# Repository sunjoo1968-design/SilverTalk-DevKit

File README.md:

# SilverTalk DevKit

제작자 SunjooAn · 갤럭시 앱 1.10 · ESP32 DevKit 펌웨어 1.8

SilverTalk는 ESP32-WROOM-32 박스의 물리 버튼으로 갤럭시에서 AI 음성 대화를 시작하고 마이크를 제어합니다. USB 또는 Wi-Fi로 박스를 연결하고, 보호자가 A·B 위치에 ChatGPT, Gemini Live, Sesame, Pi를 배정할 수 있습니다. 음성 입출력은 갤럭시의 마이크와 스피커를 사용합니다.

## 설치와 사용

[GitHub 배포 ZIP](https://github.com/sunjoo1968-design/SilverTalk-DevKit/releases/latest)에는 갤럭시 APK, 기존 박스 업데이트용 펌웨어, 새 박스 설치용 통합 펌웨어, 설치 안내와 배선도가 들어 있습니다.

- [설치와 보호자 설정](devkit-controller/docs/설치안내.md)
- [ESP32 펌웨어 플래싱 상세 안내](devkit-controller/docs/펌웨어-플래싱.md)
- [GPIO 배선도](devkit-controller/docs/배선도.svg)와 [부품표](devkit-controller/docs/부품표.md)

통화 중 대기 버튼을 3초 눌러 연속 대화를 켜고, 짧게 눌러 음소거 대기로 돌아옵니다. 선택 사양인 연속 대화 전용 버튼은 GPIO33, 전용 LED는 GPIO13에 연결합니다.

앱 1.10은 서비스 전환 중 선택이 다시 바뀌면 마지막 스위치 위치를 기준으로 통화를 유지합니다. 앱 1.9에서 수정한 짧은 Wi-Fi 지연 대응도 포함합니다. 다른 기종에서는 PD 충전과 USB 호스트 동시 동작 및 사용할 AI 앱의 마이크 제어를 설치할 때 확인하세요.

## 프로토타입 PCB

PCB r1.0은 30핀 ESP32-WROOM-32 DevKit을 두 줄의 암헤더에 끼우고, 스위치·LED·OLED를 JST XH로 연결하는 84 × 74 mm 캐리어입니다.

- [PCB 제작·조립 안내와 국내 부품 구매 링크](devkit-controller/hardware/carrier-r1.0/README.md)
- [PCB 주문용 거버 ZIP](https://github.com/sunjoo1968-design/SilverTalk-DevKit/releases/download/pcb-r1.0/SilverTalk-DevKit-Carrier-r1.0-JLCPCB-Gerber.zip)
- [KiCad 설계 전체 ZIP](https://github.com/sunjoo1968-design/SilverTalk-DevKit/releases/download/pcb-r1.0/SilverTalk-DevKit-Carrier-r1.0.zip)

## 프로토타입 케이스 r1.0

84 × 74 mm 캐리어용 본체, 교체형 전면판, 분리형 상판과 갤럭시 가로·세로 거치대를 포함합니다.

- [JLC3DP용 STL ZIP](https://github.com/sunjoo1968-design/SilverTalk-DevKit/releases/download/case-r1.0/SilverTalk-DevKit-Case-r1.0-JLC3DP.zip)
- [주문·조립 안내와 1:1 전면 도면](devkit-controller/hardware/enclosure-r1.0/README.md)

## 소스 빌드

### 갤럭시 앱

Windows PowerShell, JDK 17 이상, Android SDK Platform 36과 Build Tools 35.0.0을 사용합니다.

```powershell
.\devkit-controller\android\Build-Android.ps1 -AndroidSdk 'C:\Android\Sdk'
```

결과는 `devkit-controller/android/build/SilverTalk-DevKit-unsigned.apk`입니다. 새로 빌드한 APK는 본인 keystore로 서명할 수 있습니다. 배포 APK 위에 덮어 설치하려면 같은 서명이 필요하므로 일반 설치에는 GitHub Release의 서명된 APK를 사용하세요.

### ESP32 펌웨어

ESP-IDF 5.5.6 환경에서 실행합니다.

```powershell
Set-Location .\devkit-controller\firmware
idf.py set-target esp32
idf.py build
```

앱 영역 업데이트 파일은 `build/silvertalk_controller.bin`입니다. 초기 설치에는 `idf.py -p COM20 flash` 또는 배포 ZIP의 통합 파일을 사용합니다. COM 번호는 PC에서 확인한 값으로 바꿉니다.

## 제작 정보

음성 제어 흐름은 Sesami · ChatGPT Pro Micro V1 샘플을 참고했습니다. Android USB 시리얼 코드의 저작자와 라이선스는 [USB-SERIAL-LICENSE.txt](devkit-controller/android/USB-SERIAL-LICENSE.txt)에 있습니다.

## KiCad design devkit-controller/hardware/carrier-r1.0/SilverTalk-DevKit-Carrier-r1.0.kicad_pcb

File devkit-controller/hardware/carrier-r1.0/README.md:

# SilverTalk DevKit 캐리어 PCB r1.0

제작자 SunjooAn · 갤럭시 앱 1.10 · ESP32 DevKit 펌웨어 1.8

SilverTalk의 패널 부품을 배선 하네스로 꽂고, ESP32 DevKit을 교체할 수 있는 2층 캐리어입니다. 대상은 ESP32-WROOM-32 USB-C DevKit 중 **양쪽 15핀, 한 줄 피치 2.54 mm, 두 줄 중심 간격 25.00 mm**인 보드입니다.

## 주문 전 맞춤 확인

- 부품면에서 안테나를 위로 두었을 때 왼쪽 줄 맨 위는 `EN`, 오른쪽 줄 맨 위는 `23`입니다. USB-C 쪽 왼쪽 끝은 `VIN`, 오른쪽 끝은 `3V3`입니다. 보드의 인쇄 표기와 키캐드 회로도에서 이 방향과 실제 GPIO 순서를 확인하세요.
- [소켓 맞춤 1:1 도면](소켓맞춤-1대1.svg)을 100%로 인쇄하고, 도면의 25 mm 선을 자로 확인한 뒤 DevKit을 얹어 보세요. 두 줄 중심은 25.00 mm이며, 각 줄의 첫 핀부터 끝 핀까지는 35.56 mm입니다.
- 두 개의 독립 암헤더를 DevKit에 먼저 끼우고 캐리어의 홈에 넣어 위치를 맞춥니다. 가로 2.00 × 세로 1.00 mm 도금 슬롯 안에서 암헤더를 맞춘 다음 두 줄의 끝 핀을 먼저 납땜하세요. DevKit을 뺐다가 다시 끼워 맞춤을 확인한 뒤 나머지 핀을 납땜합니다.

## PCB 주문

JLC3DP에서 **PCB/PCBA** 메뉴를 선택하면 JLCPCB의 PCB 주문 화면으로 이동합니다. 그 화면에 `SilverTalk-DevKit-Carrier-r1.0-JLCPCB-Gerber.zip`을 올리세요. [JLC3DP 공식 주문 안내](https://jlc3dp.com/help/article/how-to-combine-orders-for-jlc3dp-and-jlcpcb-products)

| 항목 | 주문 설정 |
| --- | --- |
| 소재·층수 | FR-4, 2층 |
| 외곽 크기 | 84 × 74 mm. 위쪽 안테나 홈 36 × 12 mm, 아래쪽 USB-C 케이블 홈 14 × 12 mm |
| 형태·수량 | Standard PCB/PCBA · Single PCB · Different Design 1 · 프로토타입 5장 |
| 두께·동박 | 1.6 mm, 외층 1 oz |
| 색상·표면처리 | Green · White 실크 · LeadFree HASL |
| 조립 | PCB Assembly 끔 · Stencil 끔. 스루홀 부품은 직접 납땜 |
| 드릴 | PTH 62개 중 가로 도금 슬롯 30개, NPTH Ø3.2 mm 고정 홀 4개 |
| 슬롯 옵션 | Blind Slots No. 소켓 슬롯은 기판을 관통하는 2.00 × 1.00 mm 도금 슬롯 |
| 제조 파일 확인 | Confirm Production File Yes · Do not confirm automatically 체크 |

JLCPCB 견적 화면에서 2층과 84 × 74 mm 인식을 확인했고, 뷰어의 드릴 레이어에서 소켓 슬롯 30개와 고정 홀 4개를 확인했습니다. 주문 전 미리보기에서 같은 외곽과 홀을 대조하세요. ZIP에는 거버 7개, Excellon 드릴 2개, 거버 작업 정보가 들어 있습니다. [JLCPCB 거버·드릴 안내](https://jlcpcb.com/help/article/how-to-generate-gerber-and-drill-files-in-kicad-8) · [제조 파일 확인 안내](https://jlcpcb.com/kr/help/article/how-to-confirm-the-production-file)

## 커넥터 핀

모든 2핀 커넥터에서 **1번은 신호 또는 LED 양극, 2번은 GND**입니다. PCB의 사각 패드와 짧은 실크 표식이 1번입니다. 스위치는 닫을 때 GPIO를 GND에 연결합니다. 아래 번호는 부품면 기준입니다.

| 커넥터 | 연결 부품 | 1번 | 2번 |
| --- | --- | --- | --- |
| J3 | 서비스 B LED | GPIO32 → R1 → LED 양극 | LED 음극 |
| J4 | 연속 대화 버튼 | GPIO33 | GND |
| J5 | 말하기 PTT 버튼 | GPIO25 | GND |
| J6 | 대기 버튼 LED | GPIO26 → R2 → LED 양극 | LED 음극 |
| J7 | 대기·깨우기 버튼 | GPIO23 | GND |
| J9 | 마이크 LED | GPIO19 → R3 → LED 양극 | LED 음극 |
| J10 | 서비스 A/B 전환 스위치 | GPIO18 | GND |
| J11 | 서비스 A LED | GPIO27 → R4 → LED 양극 | LED 음극 |
| J12 | 연속 대화 LED | GPIO13 → R5 → LED 양극 | LED 음극 |

**J8 OLED**는 1번 GND, 2번 3V3, 3번 SCL(GPIO22), 4번 SDA(GPIO21)입니다. OLED 모듈에 인쇄된 이름끼리 연결하세요. 3.3 V SSD1306 I²C 128×64, 주소 0x3C를 사용합니다.

J10을 개방하면 A, GND에 연결하면 B입니다. J4·J5·J7에는 순간식 NO 버튼을 사용합니다. LED의 저항은 PCB에 장착하므로 각 LED는 해당 커넥터에 양극과 음극을 연결합니다.

## 부품표

| 수량 | 품목과 규격 |
| --- | --- |
| 1 | ESP32-WROOM-32 USB-C DevKit, 30핀, 4MB, 실물 핀 배열 확인 |
| 2 | J1·J2 — 1×15, 2.54 mm, 수직 스루홀 암헤더 |
| 9 | J3–J7, J9–J12 — JST XH 2핀 PCB 헤더 B2B-XH-A 및 짝 하우징 XHP-2 |
| 1 | J8 — JST XH 4핀 PCB 헤더 B4B-XH-A 및 짝 하우징 XHP-4 |
| 22 | JST XH 암 크림프 단자 SXH-001T-P0.6 또는 규격에 맞는 사전 압착 케이블 |
| 5 | R1–R5 — 220 Ω, 1/4 W, 축형, 리드 간격 7.62 mm |
| 5 | 5 mm LED, 낮은 순방향 전압의 고효율형 |
| 3 | 순간식 NO 버튼, 패널 장착형 |
| 1 | 유지형 SPST ON/OFF 스위치, 패널 장착형 |
| 1 | SSD1306 I²C OLED 모듈, 4선 |
| 4 | M3 스페이서와 나사, PCB 홀 Ø3.2 mm |

JST XH 커넥터의 피치는 **2.50 mm**입니다. [JST XH 공식 도면](https://www.jst-mfg.com/product/pdf/eng/eXH.pdf)

## 국내 구매와 직접 압착

다음 수량은 PCB 한 장에 모든 패널 부품을 연결하는 기준입니다.

| 부품 | 필요한 수량 | 국내 구매처 |
| --- | ---: | --- |
| ESP32 소켓. 1×15, 2.54 mm, 수직 스루홀 암헤더 | 2개 | [디바이스마트 1×15 암헤더](https://www.devicemart.co.kr/goods/view?no=12497) |
| PCB용 2핀 수헤더 `B2B-XH-A` | 9개 | [레고전자부품 B2B-XH-A](https://regoelec.co.kr/product/detail.html?product_no=3910) |
| PCB용 4핀 수헤더 `B4B-XH-A` | 1개 | [레고전자부품 B4B-XH-A](https://regoelec.co.kr/product/detail.html?product_no=3912) |
| 배선용 2핀 암 하우징 `XHP-02` | 9개 | [레고전자부품 XHP-02](https://regoelec.co.kr/product/detail.html?product_no=3905) |
| 배선용 4핀 암 하우징 `XHP-04` | 1개 | [레고전자부품 XHP-04](https://regoelec.co.kr/product/detail.html?product_no=3907) |
| 두 하우징에 공통으로 쓰는 암 압착 단자 `SXH-001T-P0.6` | 22개 | [레고전자부품 SXH-001T-P0.6](https://regoelec.co.kr/product/detail.html?product_no=3920) |

암 하우징은 각각 `1EA` 옵션을 선택하고, 압착 단자는 이 판매처의 최소 옵션인 `100EA` 한 팩을 선택합니다. 부품을 확인했을 때 하우징 10개와 단자 한 팩은 합계 2,485원이었으며, 전선과 배송비는 별도입니다.

AWG 26 연선에 암 단자를 압착하고 하우징에 끼웁니다. J8은 **1 GND, 2 3V3, 3 SCL, 4 SDA**를 기준으로 하네스 전선에 표시한 뒤 OLED 모듈의 핀 이름끼리 연결하세요.

완성 하네스를 사용할 경우에는 [로봇사이언스몰 2핀 JST XH 호환 하네스](https://robotscience.kr/goods/view?no=16652) 9세트와 [디바이스마트 4핀 JST XH 호환 하네스](https://www.devicemart.co.kr/goods/view?no=15574781) 1세트를 준비합니다. 각 세트에서 PCB의 수헤더에 꽂히는 전선 쪽 암 커넥터를 사용합니다.

## 조립 후 확인

1. 전원을 분리한 상태에서 암헤더, 저항, JST 헤더를 납땜하고 3V3와 GND 사이 단락 여부를 확인합니다.
2. 안테나가 위쪽 홈을 향하고 USB-C가 아래쪽 홈을 향하도록 DevKit을 끼웁니다. 안테나 위·뒤에 금속 스페이서, 전선 뭉치, 금속 케이스가 가까이 오지 않도록 배치합니다. [Espressif ESP32 안테나 배치 가이드](https://docs.espressif.com/projects/esp-hardware-design-guidelines/en/latest/esp32/pcb-layout-design.html)
3. 각 커넥터에 패널 부품을 꽂고 DevKit 자체 USB-C로 전원을 공급합니다. 유선 제어에는 DevKit USB-C를 기존 갤럭시 PD 허브에 연결합니다.
4. OLED 표시, A/B 전환, 대기 버튼, PTT, 연속 대화 버튼과 해당 LED를 차례로 확인합니다. 펌웨어는 기존 1.8을 그대로 사용합니다. [펌웨어 플래싱 안내](펌웨어-플래싱.md)

## 설계 검증

KiCad 9.0.8에서 전기 규칙 검사(ERC), PCB 설계 규칙 검사(DRC), 회로도와 PCB 대조를 실행했습니다. 각각 0건이며 미연결 패드도 0건입니다. 제조용 거버 외곽은 84 × 74 mm이고, 별도 드릴 파일에 도금 슬롯 30개와 비도금 Ø3.2 mm 홀 4개가 있습니다. 실물 소켓 맞춤과 제작 후 기능 검증은 프로토타입 조립 때 확인합니다.

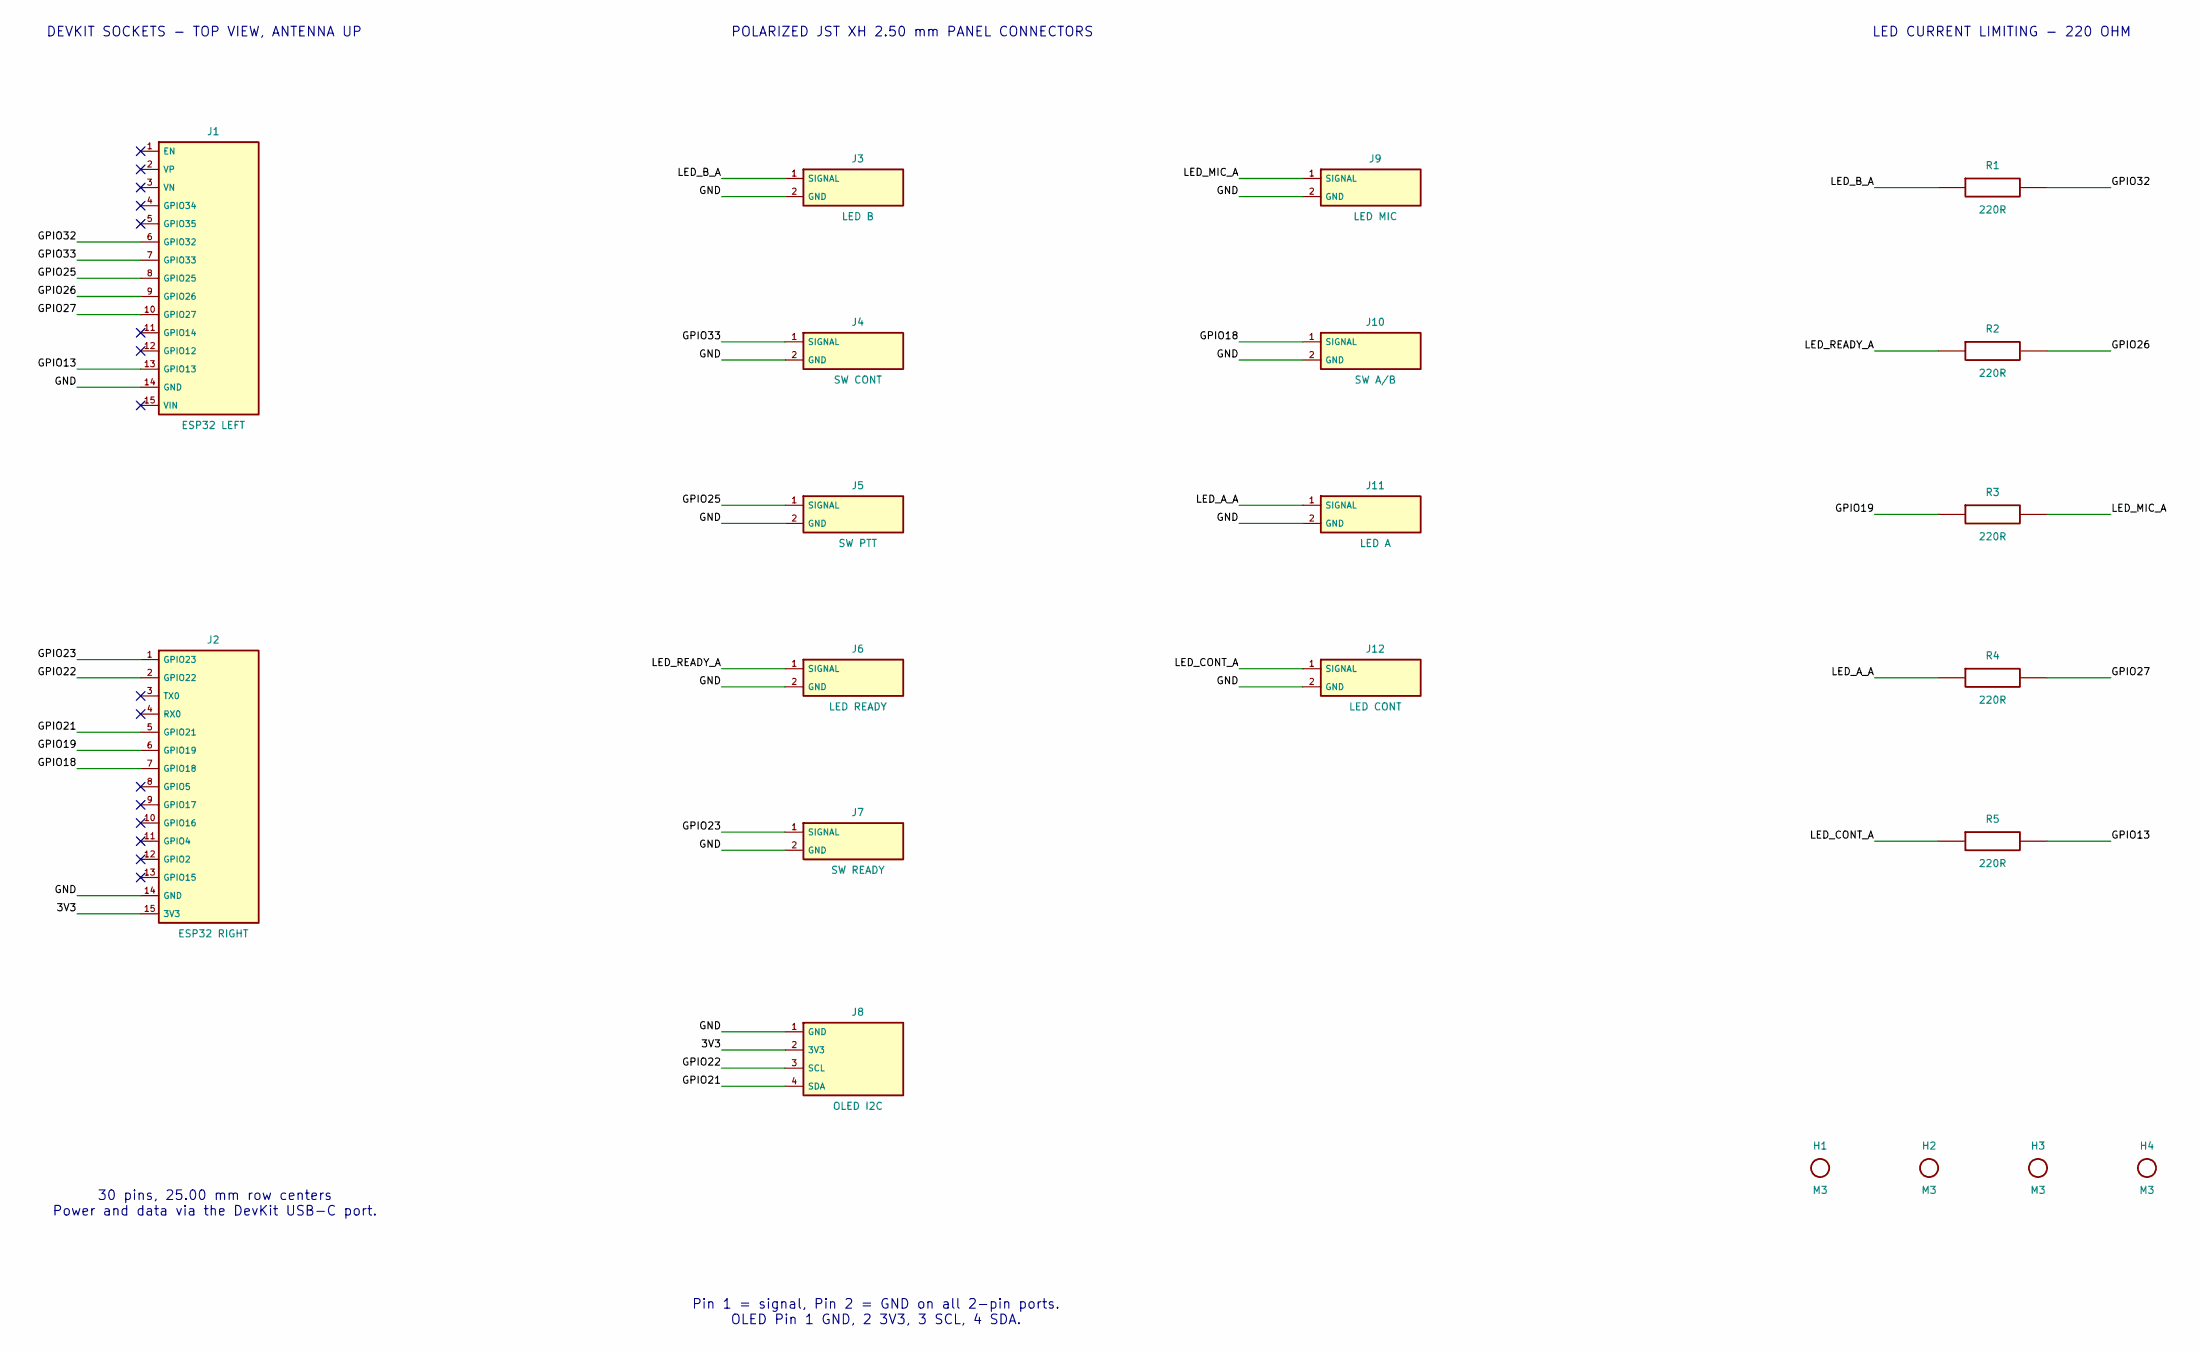
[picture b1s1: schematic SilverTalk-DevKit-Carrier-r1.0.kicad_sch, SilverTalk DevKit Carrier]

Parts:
H1, H2, H3, H4: M3; MountingHole_3.2_M3
J1: ESP32 LEFT; Socket_1x15_P2.54_LateralSlots
J2: ESP32 RIGHT; Socket_1x15_P2.54_LateralSlots
J3: LED B; JST_XH_1x02
J4: SW CONT; JST_XH_1x02
J5: SW PTT; JST_XH_1x02
J6: LED READY; JST_XH_1x02
J7: SW READY; JST_XH_1x02
J8: OLED I2C; JST_XH_1x04
J9: LED MIC; JST_XH_1x02
J10: SW A/B; JST_XH_1x02
J11: LED A; JST_XH_1x02
J12: LED CONT; JST_XH_1x02
R1, R2, R3, R4, R5: 220R; R_Axial_P7.62

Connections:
/3V3: J2.15 (3V3), J8.2 (3V3)
/GND: J1.14 (GND), J2.14 (GND), J3.2 (GND), J4.2 (GND), J5.2 (GND), J6.2 (GND), J7.2 (GND), J8.1 (GND), J9.2 (GND), J10.2 (GND), J11.2 (GND), J12.2 (GND)
/GPIO13: J1.13 (GPIO13), R5.2
/GPIO18: J2.7 (GPIO18), J10.1 (SIGNAL)
/GPIO19: J2.6 (GPIO19), R3.1
/GPIO21: J2.5 (GPIO21), J8.4 (SDA)
/GPIO22: J2.2 (GPIO22), J8.3 (SCL)
/GPIO23: J2.1 (GPIO23), J7.1 (SIGNAL)
/GPIO25: J1.8 (GPIO25), J5.1 (SIGNAL)
/GPIO26: J1.9 (GPIO26), R2.2
/GPIO27: J1.10 (GPIO27), R4.2
/GPIO32: J1.6 (GPIO32), R1.2
/GPIO33: J1.7 (GPIO33), J4.1 (SIGNAL)
/LED_A_A: J11.1 (SIGNAL), R4.1
/LED_B_A: J3.1 (SIGNAL), R1.1
/LED_CONT_A: J12.1 (SIGNAL), R5.1
/LED_MIC_A: J9.1 (SIGNAL), R3.2
/LED_READY_A: J6.1 (SIGNAL), R2.1

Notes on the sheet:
DEVKIT SOCKETS - TOP VIEW, ANTENNA UP
POLARIZED JST XH 2.50 mm PANEL CONNECTORS
LED CURRENT LIMITING - 220 OHM
Pin 1 = signal, Pin 2 = GND on all 2-pin ports. OLED Pin 1 GND, 2 3V3, 3 SCL, 4 SDA.
30 pins, 25.00 mm row centers Power and data via the DevKit USB-C port.

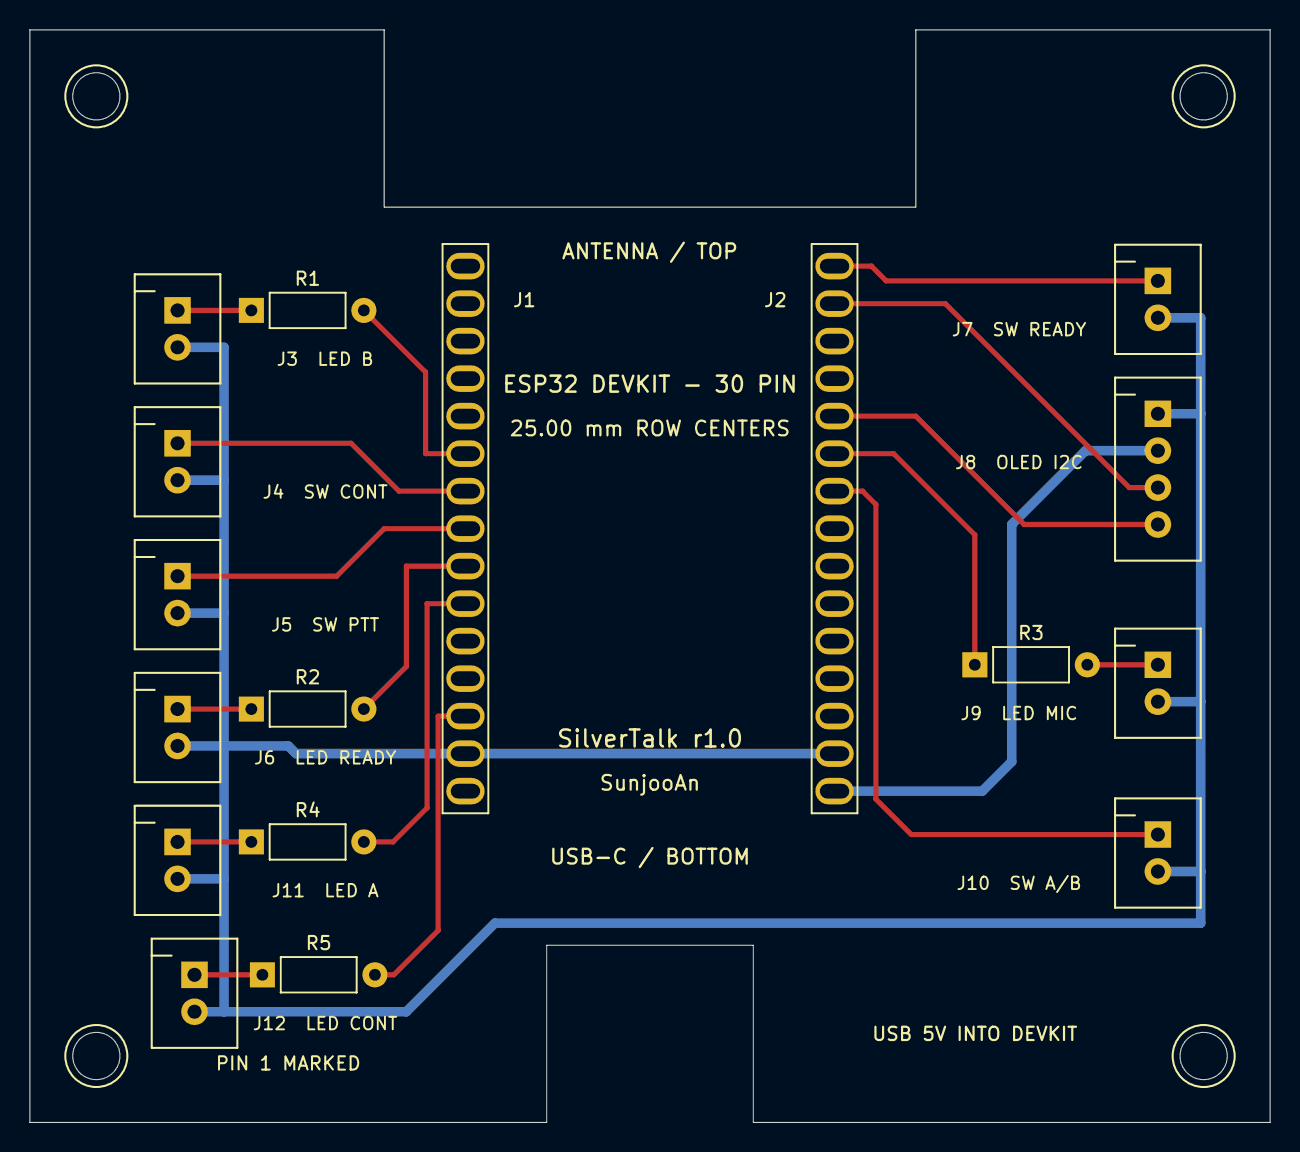
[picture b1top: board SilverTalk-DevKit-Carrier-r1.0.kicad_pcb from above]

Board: 2 copper layers, 84.0 x 74.0 mm, 21 parts (0 on the bottom side), 18 nets.
